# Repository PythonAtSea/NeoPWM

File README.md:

# NeoPWM
### The best led controller for FTC
> [!NOTE]
> This is a [Highway](https://highway.hackclub.com) project, if you're here from slack (or just want to see the process of development) see [JOURNAL.md](https://github.com/PythonAtSea/NeoPWM/blob/main/JOURNAL.md), for the BOM see [BOM.md](https://github.com/PythonAtSea/NeoPWM/blob/main/BOM.md)

> [!CAUTION]
> Curently the PCB has the USB data lines swapped, will fix soon™

##### What is it?
The NeoPWM is a PWM controlled, USB-C powered, highly configurable SK6812/WS2801 (NeoPixel) controller designed for the _FIRST_ Tech Challenge (FTC). It will have a web based tool to generate configuration files and send over a serial interface. It will have poweron and PWM signal loss states, which allow led patterns to be triggered after a match and during the transition period. It also has a optional intergrated LED panel with 12 SK6812 LEDs, which will have prebuilt patterns. 
##### Why did I make it?
In FTC, there was never a great way to control LEDs. YOu could control a strip of leds over I2C using a [I2C to NeoPixel driver](https://www.adafruit.com/product/5766), but the I2C ports on the [REV Control Hub ](https://www.revrobotics.com/rev-31-1595/) are slow, which ruins your loop times which causes problems with odometry. You could use the [REV Blinkin](https://www.revrobotics.com/rev-11-1105/)
 (no that's not a typo) which is controlled over I2C, but you can't do any configuration and it's powered from the main robot battery. The NeoPWM can be powered from a external USB-C battery and will have a web tool to configure the patterns, and it will have a intergrated LED panel like the [CTRE CANdle](https://store.ctr-electronics.com/products/candle), but it will be optional, saving costs for teams who just want a LED strip.
 
**NeoPWM in default configuration without LED panel.**

**NeopPWM with intergrated LED panel**

**Both PCBs connected with 2mm mousebites**

**Main schematic**

**RP2040 circuitry schematic**

## BOM
| Name | Link | Price |
| --- | ---| --: |
| PCB | N/A | $2.00 |
| PCB Assembly | N/A | $31.64 |
| JLC Shipping | N/A | $52.31 |
| JLC Total | N/A | $76.95 |
| JST PH Connector | https://www.digikey.com/en/products/detail/jst-sales-america-inc/S3B-PH-K-S/926627 | $1.31 |
| DuPont connector | https://www.digikey.com/en/products/detail/amphenol-cs-fci/68604-403HLF/5206799 | $1.15 |
| Sk6812 Strip | https://www.digikey.com/en/products/detail/dfrobot/FIT0750/14322609 | $23.62 |
| DigiKey Shipping | N/A | $6.99 |
| DigiKey Total | N/A | $37.91 |
| M2 Screws | https://www.aliexpress.com/item/3256806025233809.html | $1.34 |
| M2 Standoffs | https://www.aliexpress.com/item/3256804631738035.html | $2.46 |
| Aliexpress Total | N/A | $3.80 |

> [!CAUTION]
> This project has not been built physically, so it may or may not work as intended.

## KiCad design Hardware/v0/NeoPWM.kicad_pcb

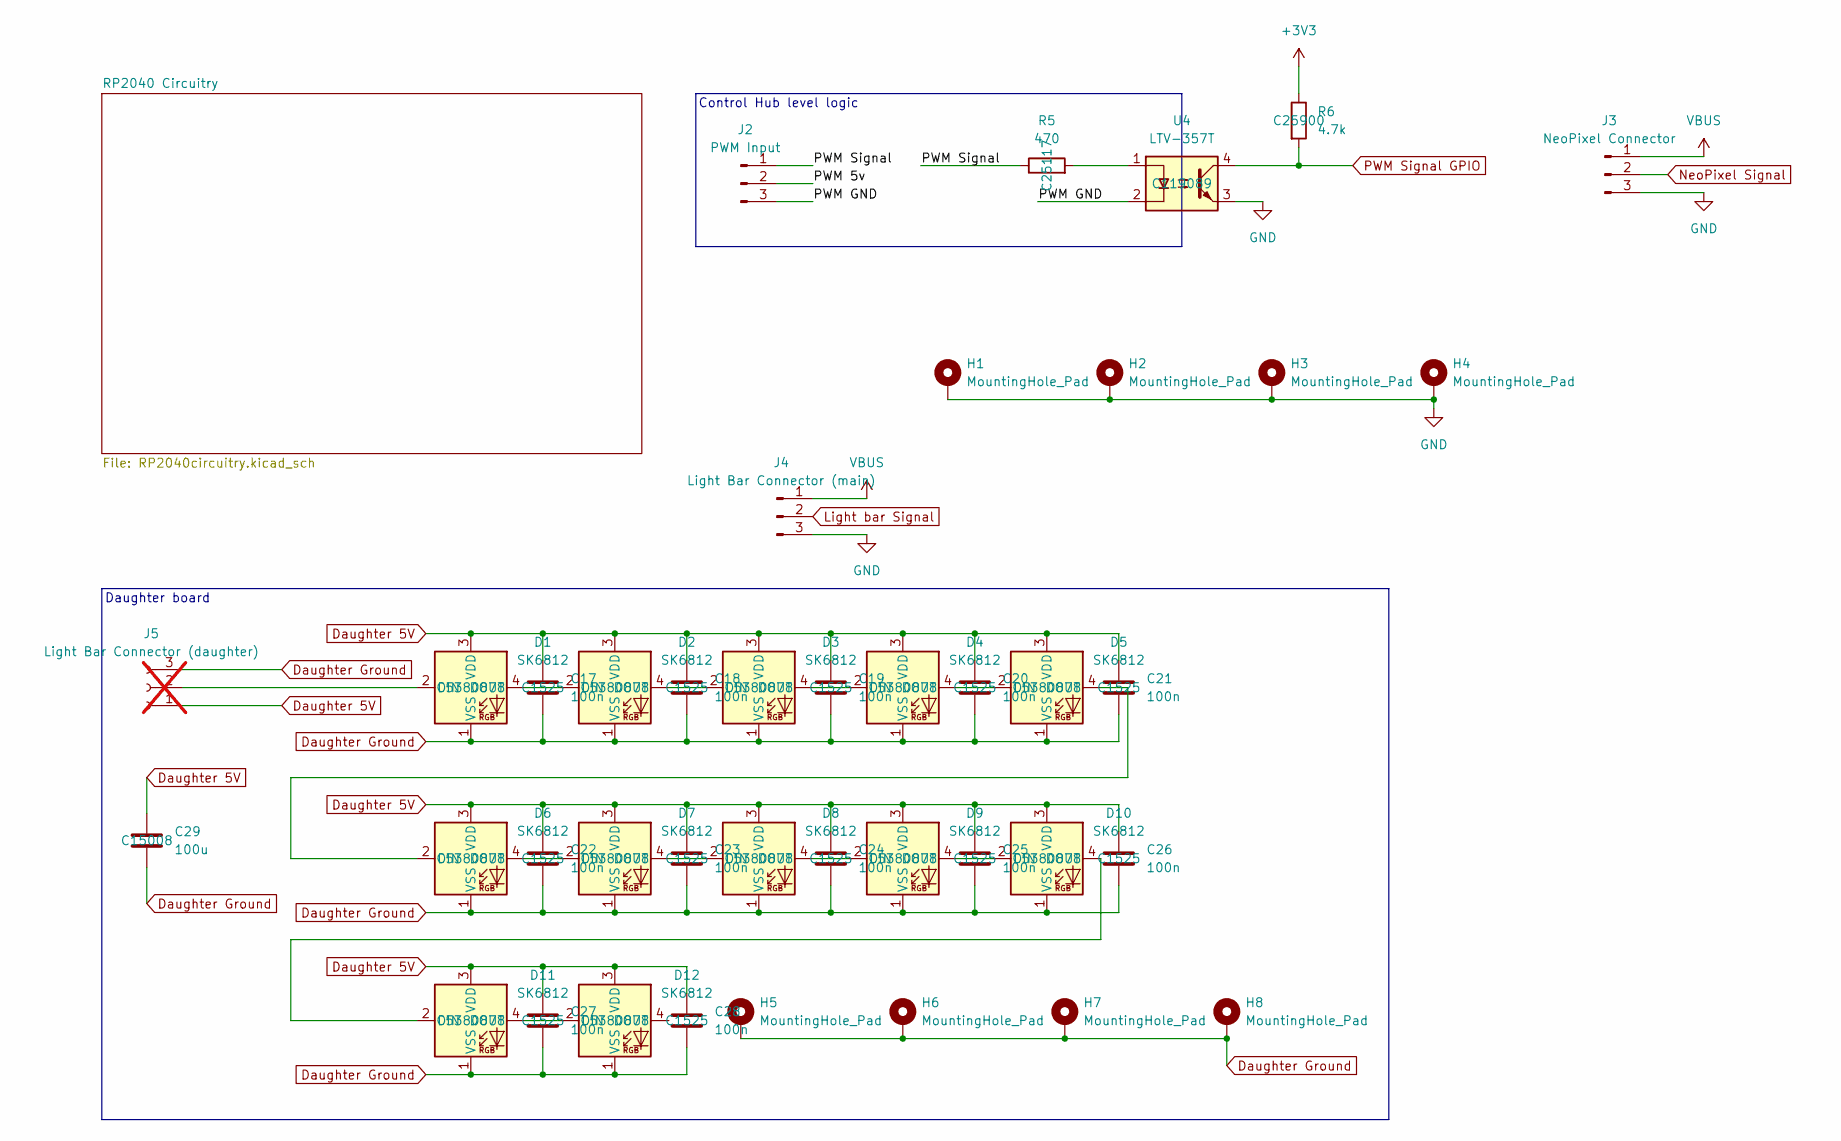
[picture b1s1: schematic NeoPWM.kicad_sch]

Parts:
C17, C18, C19, C20, C21, C22, C23, C24, C25, C26, C27, C28: 100n; C_0402_1005Metric; LCSC C1525
C29: 100u; C_1206_3216Metric; LCSC C15008
D1, D2, D3, D4, D5, D6, D7, D8, D9, D10, D11, D12: SK6812; LED_SK6812_PLCC4_5.0x5.0mm_P3.2mm; LCSC C5380878
H1, H2, H3, H4, H5, H6, H7, H8: MountingHole_Pad; MountingHole_2.2mm_M2_Pad
J2: PWM Input; JST_PH_S3B-PH-K_1x03_P2.00mm_Horizontal
J3: NeoPixel Connector; JST_PH_S3B-PH-K_1x03_P2.00mm_Horizontal
J4: Light Bar Connector (main); PinHeader_1x03_P2.54mm_Vertical
J5: Light Bar Connector (daughter); PinSocket_1x03_P2.54mm_Vertical; not fitted
R5: 470; R_0402_1005Metric; LCSC C25117
R6: 4.7k; R_0402_1005Metric; LCSC C25900
U4: LTV-357T; LTV-357T_LTO; LCSC C119089

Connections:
+3V3: R6.1; also elsewhere on the board
/PWM 5v: J2.2
/PWM GND: J2.3, U4.2
/PWM Signal: J2.1, R5.1
Daughter 5V: C17.1, C18.1, C19.1, C20.1, C21.1, C22.1, C23.1, C24.1, C25.1, C26.1, C27.1, C28.1, C29.1, D1.3 (VDD), D2.3 (VDD), D3.3 (VDD), D4.3 (VDD), D5.3 (VDD), D6.3 (VDD), D7.3 (VDD), D8.3 (VDD), D9.3 (VDD), D10.3 (VDD), D11.3 (VDD), D12.3 (VDD), J5.1
Daughter Ground: C17.2, C18.2, C19.2, C20.2, C21.2, C22.2, C23.2, C24.2, C25.2, C26.2, C27.2, C28.2, C29.2, D1.1 (VSS), D2.1 (VSS), D3.1 (VSS), D4.1 (VSS), D5.1 (VSS), D6.1 (VSS), D7.1 (VSS), D8.1 (VSS), D9.1 (VSS), D10.1 (VSS), D11.1 (VSS), D12.1 (VSS), H5.1, H6.1, H7.1, H8.1, J5.3
GND: H1.1, H2.1, H3.1, H4.1, J3.3, J4.3, U4.3; also elsewhere on the board
Light bar Signal: J4.2; also elsewhere on the board
NeoPixel Signal: J3.2; also elsewhere on the board
unnamed: D1.2 (DIN), J5.2
unnamed: D1.4 (DOUT), D2.2 (DIN)
unnamed: D2.4 (DOUT), D3.2 (DIN)
unnamed: D3.4 (DOUT), D4.2 (DIN)
unnamed: D4.4 (DOUT), D5.2 (DIN)
unnamed: D5.4 (DOUT), D6.2 (DIN)
unnamed: D6.4 (DOUT), D7.2 (DIN)
unnamed: D7.4 (DOUT), D8.2 (DIN)
unnamed: D8.4 (DOUT), D9.2 (DIN)
unnamed: D9.4 (DOUT), D10.2 (DIN)
unnamed: D10.4 (DOUT), D11.2 (DIN)
unnamed: D11.4 (DOUT), D12.2 (DIN)
unnamed: R5.2, U4.1
PWM Signal GPIO: R6.2, U4.4; also elsewhere on the board
VBUS: J3.1, J4.1; also elsewhere on the board

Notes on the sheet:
Daughter board
Control Hub level logic

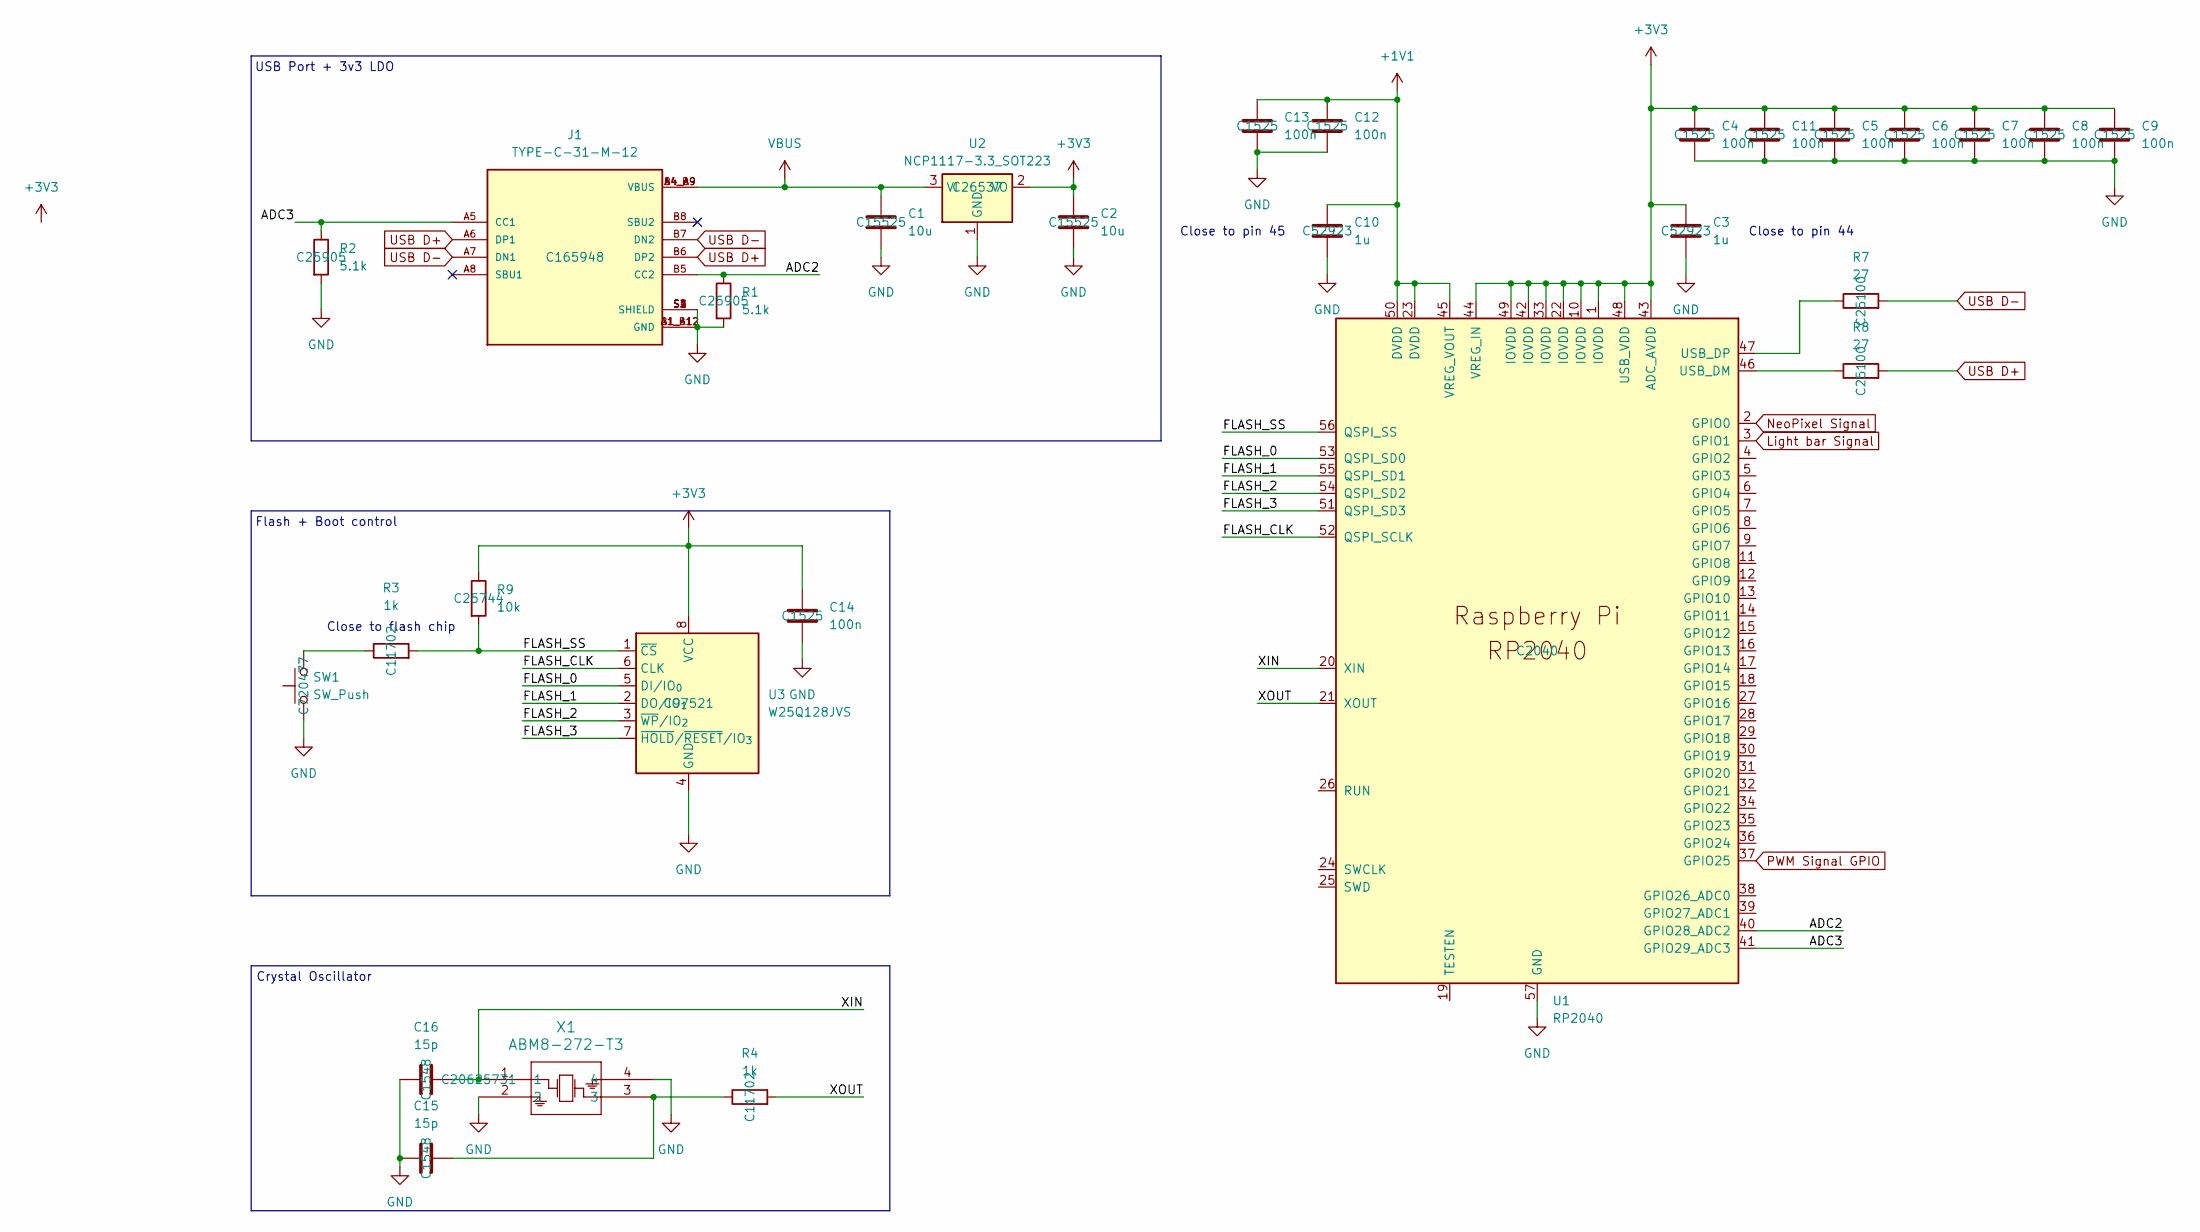
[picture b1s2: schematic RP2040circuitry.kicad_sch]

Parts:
C1, C2: 10u; C_0402_1005Metric; LCSC C15525
C3, C10: 1u; C_0402_1005Metric; LCSC C52923
C4, C5, C6, C7, C8, C9, C11, C12, C13, C14: 100n; C_0402_1005Metric; LCSC C1525
C15, C16: 15p; C_0402_1005Metric; LCSC C1548
J1: TYPE-C-31-M-12; HRO_TYPE-C-31-M-12; PARTREV 2020.12.08; LCSC C165948
R1, R2: 5.1k; R_0402_1005Metric; LCSC C25905
R3, R4: 1k; R_0402_1005Metric; LCSC C11702
R7, R8: 27; R_0402_1005Metric; LCSC C25100
R9: 10k; R_0402_1005Metric; LCSC C25744
SW1: SW_Push; SW_TS-1088_XNP-L; LCSC C720477
U1: RP2040; RP2040-QFN-56; LCSC C2040
U2: NCP1117-3.3_SOT223; SOT-223-3_TabPin2; LCSC C26537
U3: W25Q128JVS; SOIC-8_5.3x5.3mm_P1.27mm; LCSC C97521
X1: ABM8-272-T3; ABM8-272-T3_ABR; LCSC C20625731

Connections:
+1V1: C10.1, C12.1, C13.1, U1.23 (DVDD), U1.45 (VREG_VOUT), U1.50 (DVDD)
+3V3: C2.1, C3.1, C4.1, C5.1, C6.1, C7.1, C8.1, C9.1, C11.1, C14.1, R9.1, U1.1 (IOVDD), U1.10 (IOVDD), U1.22 (IOVDD), U1.33 (IOVDD), U1.42 (IOVDD), U1.43 (ADC_AVDD), U1.44 (VREG_IN), U1.48 (USB_VDD), U1.49 (IOVDD), U2.2 (VO), U3.8 (VCC); also elsewhere on the board
/RP2040 Circuitry/ADC2: J1.B5 (CC2), R1.1, U1.40 (GPIO28_ADC2)
/RP2040 Circuitry/ADC3: J1.A5 (CC1), R2.1, U1.41 (GPIO29_ADC3)
/RP2040 Circuitry/FLASH_0: U1.53 (QSPI_SD0), U3.5 (DI/IO_{0})
/RP2040 Circuitry/FLASH_1: U1.55 (QSPI_SD1), U3.2 (DO/IO_{1})
/RP2040 Circuitry/FLASH_2: U1.54 (QSPI_SD2), U3.3 (~WP/IO_{2})
/RP2040 Circuitry/FLASH_3: U1.51 (QSPI_SD3), U3.7 (~HOLD/~RESET/IO_{3})
/RP2040 Circuitry/FLASH_CLK: U1.52 (QSPI_SCLK), U3.6 (CLK)
/RP2040 Circuitry/FLASH_SS: R3.2, R9.2, U1.56 (QSPI_SS), U3.1 (~CS)
/RP2040 Circuitry/XIN: C16.2, U1.20 (XIN), X1.1
/RP2040 Circuitry/XOUT: R4.2, U1.21 (XOUT)
GND: C1.2, C2.2, C3.2, C4.2, C5.2, C6.2, C7.2, C8.2, C9.2, C10.2, C11.2, C12.2, C13.2, C14.2, C15.1, C16.1, J1.A1_B12 (GND), J1.B1_A12 (GND), J1.S1 (SHIELD), J1.S2 (SHIELD), J1.S3 (SHIELD), J1.S4 (SHIELD), R1.2, R2.2, SW1.1, U1.57 (GND), U2.1 (GND), U3.4 (GND), X1.2, X1.4; also elsewhere on the board
Light bar Signal: U1.3 (GPIO1); also elsewhere on the board
NeoPixel Signal: U1.2 (GPIO0); also elsewhere on the board
unnamed: C15.2, R4.1, X1.3
unnamed: R3.1, SW1.2
unnamed: R8.1, U1.46 (USB_DM)
unnamed: R7.1, U1.47 (USB_DP)
PWM Signal GPIO: U1.37 (GPIO25); also elsewhere on the board
USB D+: J1.A6 (DP1), J1.B6 (DP2), R8.2
USB D-: J1.A7 (DN1), J1.B7 (DN2), R7.2
VBUS: C1.1, J1.A4_B9 (VBUS), J1.B4_A9 (VBUS), U2.3 (VI); also elsewhere on the board

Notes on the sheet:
USB Port + 3v3 LDO
Close to pin 45
Close to flash chip
Crystal Oscillator
Flash + Boot control
Close to pin 44

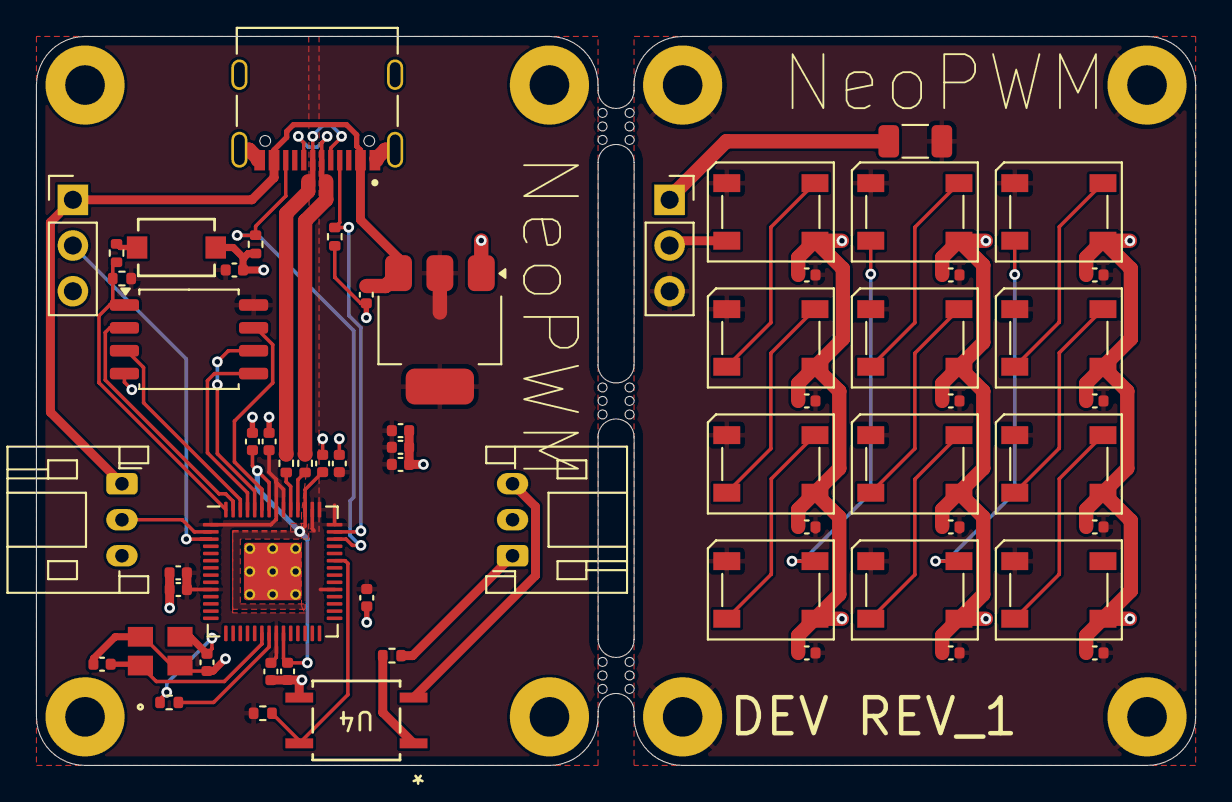
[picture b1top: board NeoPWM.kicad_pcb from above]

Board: 2 copper layers, 64.4 x 40.5 mm, 72 parts (0 on the bottom side), 40 nets.

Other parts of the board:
mouse-bite-2mm-slot, mouse-bite-2mm-slot#2, mouse-bite-2mm-slot#3: VAL**; mouse-bite-2mm-slot

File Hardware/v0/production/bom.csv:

Designator,Footprint,Quantity,Value,LCSC Part #
"C1, C2",0402,2,10u,C15525
"C10, C3",0402,2,1u,C52923
"C11, C12, C13, C14, C17, C18, C19, C20, C21, C22, C23, C24, C25, C26, C27, C28, C4, C5, C6, C7, C8, C9",0402,22,100n,C1525
"C15, C16",0402,2,15p,C1548
C29,1206,1,100u,C15008
"D1, D10, D11, D12, D2, D3, D4, D5, D6, D7, D8, D9",LED_SK6812_PLCC4_5.0x5.0mm_P3.2mm,12,SK6812,C5380878
J1,HRO_TYPE-C-31-M-12,1,TYPE-C-31-M-12,C165948
"MOUSE-BITE-2MM-SLOT_3, MOUSE-BITE-2MM-SLOT_2, MOUSE-BITE-2MM-SLOT",mouse-bite-2mm-slot,3,VAL**,
"R1, R2",0402,2,5.1k,C25905
"R3, R4",0402,2,1k,C11702
R5,0402,1,470,C25117
R6,0402,1,4.7k,C25900
"R7, R8",0402,2,27,C25100
R9,0402,1,10k,C25744
SW1,SW_TS-1088_XNP-L,1,SW_Push,C720477
U1,RP2040-QFN-56,1,RP2040,C2040
U2,SOT-223-3_TabPin2,1,NCP1117-3.3_SOT223,C26537
U3,SOIC-8_5.3x5.3mm_P1.27mm,1,W25Q128JVS,C97521
U4,LTV-357T_LTO,1,LTV-357T,C119089
X1,ABM8-272-T3_ABR,1,ABM8-272-T3,C20625731

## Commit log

2025-05-17 added overall diagram
2025-05-17 usbc stuff
2025-05-17 Update JOURNAL.md to reorganize sections and add details on USB-C port and MCU choice
2025-05-17 Fix typo in JOURNAL.md regarding MCU legal requirements
2025-05-17 Add initial KiCAD project files and update JOURNAL.md with KiCAD VCS information
2025-05-17 Add KiCAD project files, update schematic and backup configurations
2025-05-17 Add lock file pattern to .gitignore
2025-05-17 remove lock file
2025-05-17 Rename "RP2040 stuff" to "RP2040 Circuitry" in schematic and project files
2025-05-17 Refactor code structure and remove redundant sections for improved readability and maintainability
2025-05-17 Added shematic changes!
2025-05-17 Added schematic screenshot
2025-05-18 added crystal osccillator
2025-05-18 updated thingy
2025-05-19 Power + Optocoupler
2025-05-19 added image
2025-05-19 BOM + footprints
2025-05-20 3D Models
2025-05-20 3D models docs
2025-05-20 Finished schematic
2025-05-20 TODO
2025-05-20 image fix?
2025-05-20 more images!
2025-05-20 5/20 journal thingy
2025-05-20 ahaha
2025-06-01 stuff
2025-06-02 moved hardware to it's own dir
2025-06-02 images
2025-06-03 case
2025-06-03 another fix i hate markdown
2025-06-03 journal
2025-06-03 pictures!
2025-06-04 screenshot
2025-06-06 whoops i forgot to commit this
2025-06-06 fab export
2025-06-07 first draft of bom
2025-06-07 time keeps on ticking, ticking, ticking, into the future
2025-06-20 ahhh
